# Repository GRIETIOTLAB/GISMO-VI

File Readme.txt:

This folder contains flies related to the INMP441 MEMS microphone
The contents of this folder are:
- Basec read
- Basic read + OLED
- Basic read + OLED + Firebase
- Sample Bell sound file for testing

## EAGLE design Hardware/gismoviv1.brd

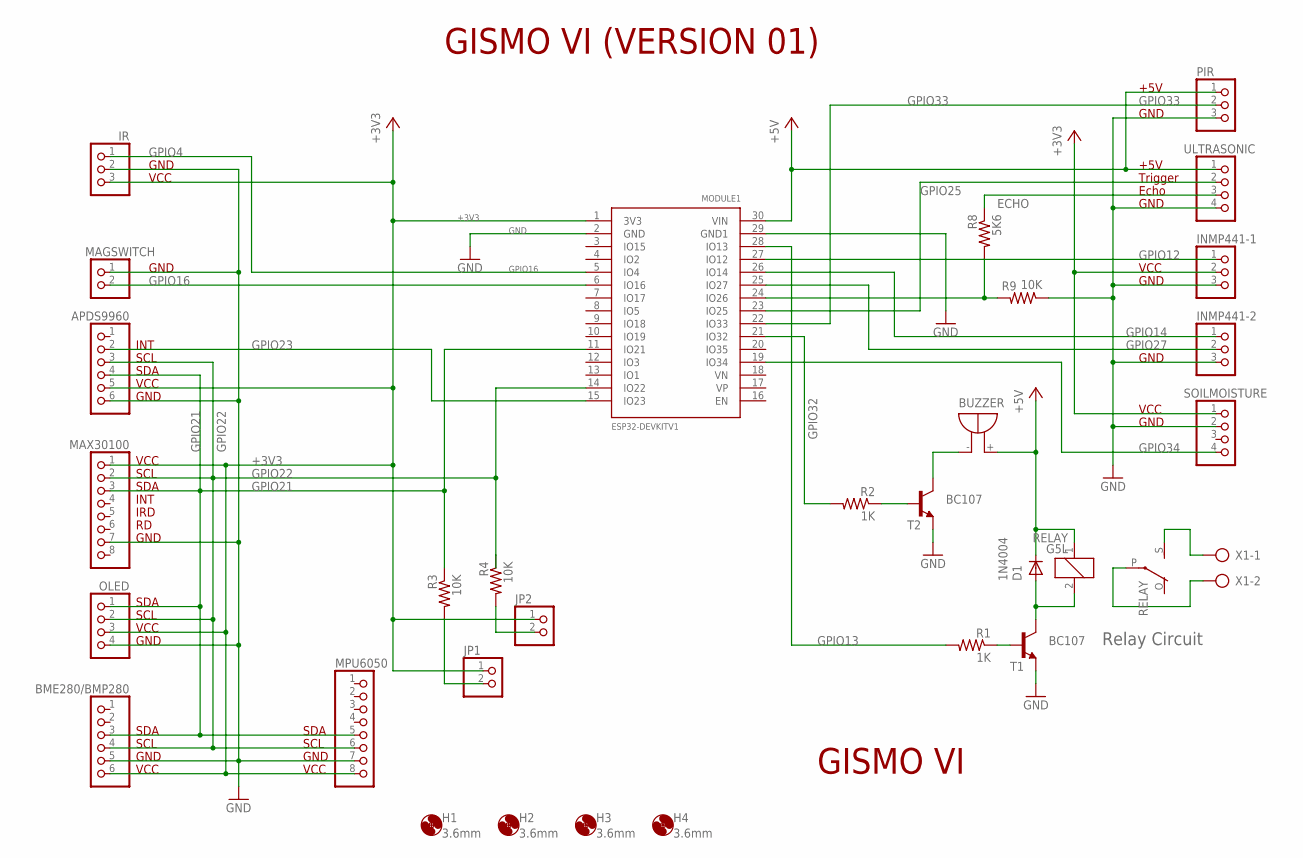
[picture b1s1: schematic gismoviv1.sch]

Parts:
APDS9960: PINHD-1X6; 1X06
BME280/BMP280: PINHD-1X6; 1X06
BUZZER: F/QMB
D1: 1N4004; DO41-10
H1, H2, H3, H4: 3.6mm; 3,6
INMP441-1, INMP441-2: PINHD-1X3; 1X03
IR: PINHD-1X3; 1X03
JP1, JP2: PINHD-1X2; 1X02
MAGSWITCH: PINHD-1X2; 1X02
MAX30100: PINHD-1X8; 1X08
MODULE1: ESP32DEVKITV1; ESP32-DEVKITV1
MPU6050: PINHD-1X8; 1X08
OLED: PINHD-1X4; 1X04
PIR: PINHD-1X3; 1X03
R1, R2: 1K; 0204/7
R3, R4, R9: 10K; 0204/7
R8: 5K6; 0204/7
RELAY: G5L; G5LE
SOILMOISTURE: PINHD-1X4; 1X04
T1, T2: BC107; TO18
ULTRASONIC: PINHD-1X4; 1X04
X1: AK500/2

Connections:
+3V3: APDS9960.5, BME280/BMP280.6, INMP441-1.2, IR.3, JP1.1, JP2.1, MAX30100.1, MODULE1.1 (3V3), MPU6050.8, OLED.3, SOILMOISTURE.1
+5V: BUZZER.+ (-), D1.C, MODULE1.30 (VIN), PIR.1, RELAY.1, ULTRASONIC.1
BUZZERCONTROL: R2.1, T2.2 (B)
BUZZERGROUND: BUZZER.- (+), T2.3 (C)
ECHO: R8.1, ULTRASONIC.3
GND: APDS9960.6, BME280/BMP280.5, INMP441-1.3, INMP441-2.3, IR.2, MAGSWITCH.1, MAX30100.7, MODULE1.2 (GND), MODULE1.29 (GND1), MPU6050.7, OLED.4, PIR.3, R9.1, SOILMOISTURE.2, T1.1 (E), T2.1 (E), ULTRASONIC.4
GPIO4: IR.1, MODULE1.5 (IO4)
GPIO12: INMP441-1.1, MODULE1.27 (IO12)
GPIO13: MODULE1.28 (IO13), R1.2
GPIO14: INMP441-2.1, MODULE1.26 (IO14)
GPIO16: MAGSWITCH.2, MODULE1.6 (IO16)
GPIO21: APDS9960.4, BME280/BMP280.3, MAX30100.3, MODULE1.11 (IO21), MPU6050.5, OLED.1, R3.1
GPIO22: APDS9960.3, BME280/BMP280.4, MAX30100.2, MODULE1.14 (IO22), MPU6050.6, OLED.2, R4.1
GPIO23: APDS9960.2, MODULE1.15 (IO23)
GPIO25: MODULE1.23 (IO25), ULTRASONIC.2
GPIO26: MODULE1.24 (IO26), R8.2, R9.2
GPIO27: INMP441-2.2, MODULE1.25 (IO27)
GPIO32: MODULE1.21 (IO32), R2.2
GPIO33: MODULE1.22 (IO33), PIR.2
GPIO34: MODULE1.19 (IO34), SOILMOISTURE.4
unnamed: JP1.2, R3.2
unnamed: JP2.2, R4.2
unnamed: D1.A, RELAY.2, T1.3 (C)
unnamed: RELAY.P, X1.2
unnamed: RELAY.S, X1.1
unnamed: R1.1, T1.2 (B)

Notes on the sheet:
Relay Circuit
GISMO VI (VERSION 01)
VCC
GND
+5V
Trigger
Echo
SDA
SCL
GISMO VI
INT
IRD

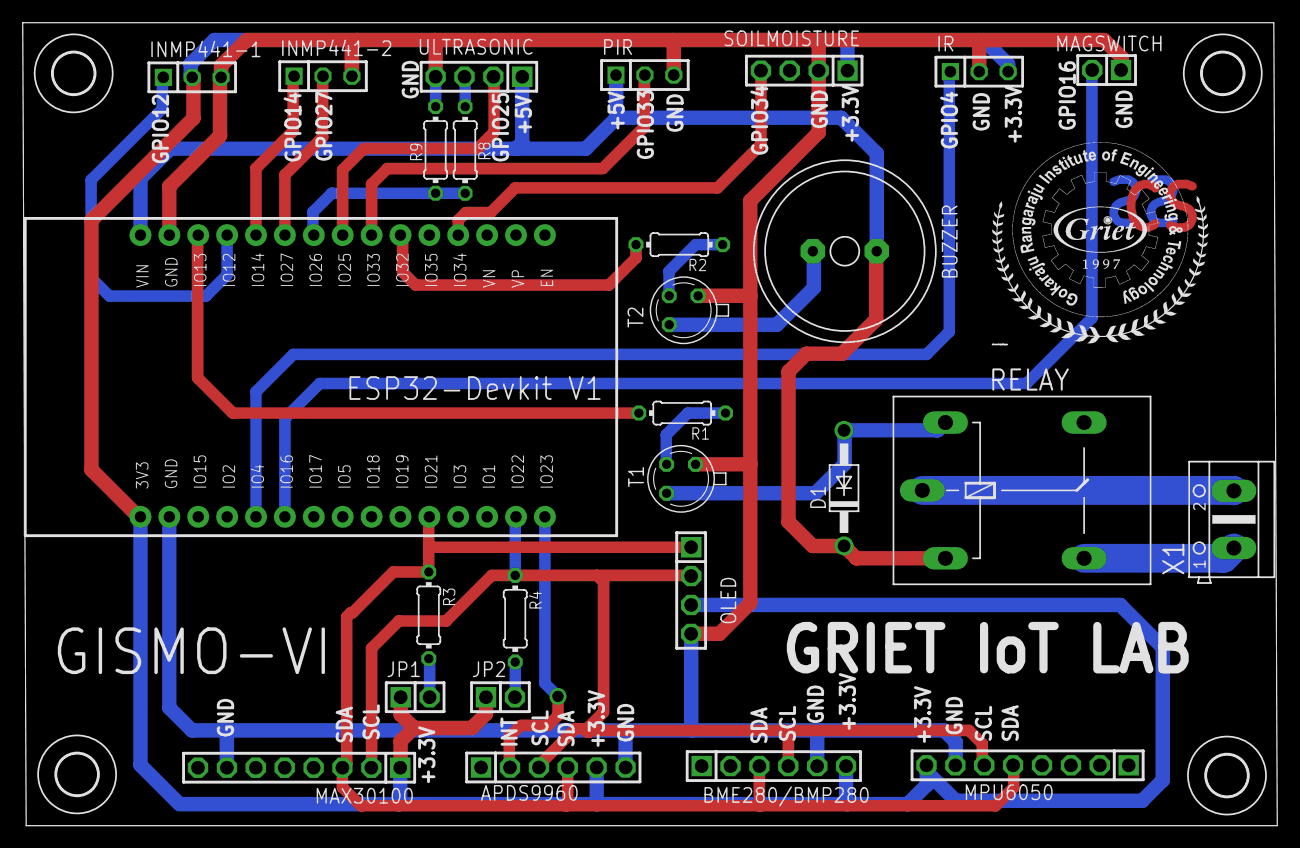
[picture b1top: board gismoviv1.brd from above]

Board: 2 copper layers, 110.3 x 70.6 mm, 32 parts (0 on the bottom side), 26 nets.

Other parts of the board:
U$1: LOGOSMALL

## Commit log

2022-06-22 Created using Colaboratory
